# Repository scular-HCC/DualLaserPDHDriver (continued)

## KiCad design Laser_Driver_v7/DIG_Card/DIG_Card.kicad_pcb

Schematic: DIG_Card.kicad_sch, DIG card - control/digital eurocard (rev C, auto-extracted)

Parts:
A1: TEENSY_4.1; TEENSY_LONG_EXT
C80, C82, C84, C85: 100n; C_0805_2012Metric_Pad1.18x1.45mm_HandSolder
C81, C86: 100nF; C_0805_2012Metric_Pad1.18x1.45mm_HandSolder
C83, C87: 10n; C_0805_2012Metric_Pad1.18x1.45mm_HandSolder
C88, C92: 0.1uF; C_0805_2012Metric_Pad1.18x1.45mm_HandSolder
C89, C90, C91: 10nF; C_0805_2012Metric_Pad1.18x1.45mm_HandSolder
C301: 100nF U301 +15V; C_0805_2012Metric
C302: 100nF U301 -15V; C_0805_2012Metric
C303: 1n ERR1 ADC filter; C_0805_2012Metric
C304: 1n ERR2 ADC filter; C_0805_2012Metric
C305: 100nF U302 +15V; C_0805_2012Metric
C306: 100nF U302 -15V; C_0805_2012Metric
C307: 100nF U303 3V3; C_0805_2012Metric
C310: DNP MOD1 LPF; C_0805_2012Metric
C311: DNP MOD2 LPF; C_0805_2012Metric
C312: 100nF Y1 3V3_OSC; C_0805_2012Metric; MPN CL21B104KBCNNNC
C313: 1uF Y1 3V3_OSC; C_0805_2012Metric; MPN CC0805KKX7R8BB105
C314: 100nF U40 3V3; C_0805_2012Metric; MPN CL21B104KBCNNNC
C315: 100nF U41 3V3; C_0805_2012Metric; MPN CL21B104KBCNNNC
C316: 100nF U42 1V8; C_0805_2012Metric; MPN CL21B104KBCNNNC
C317: 100nF U42 3V3; C_0805_2012Metric; MPN CL21B104KBCNNNC
C318: 10uF U42 3V3; C_0805_2012Metric; MPN CC0805KKX5R7BB106
C319: 1uF U42 1V8_CLK; C_0805_2012Metric; MPN CC0805KKX7R8BB105
C320: 10nF U34 COMP; C_0805_2012Metric
C321: 10nF U39 COMP; C_0805_2012Metric
C322: 10uF +5V bulk; C_0805_2012Metric
C323: 10uF 3V3 bulk; C_0805_2012Metric
C324: 100nF 1V8 entry; C_0805_2012Metric
C325: 10uF 1V8 entry; C_0805_2012Metric
D24: BAV99; SOT-23
D301: BAT54S ERR1 ADC clamp; SOT-23
D302: BAT54S ERR2 ADC clamp; SOT-23
D303, D304, D305, D306, D307, D308, D309, D310, D311: BAT54WS VM fault OR; D_SOD-323
FB301: 600R@100MHz FB Y1; L_0805_2012Metric; MPN MPZ2012S601AT000
FB302: 600R@100MHz FB U42core; L_0805_2012Metric; MPN MPZ2012S601AT000
H1, H2: MountingHole; MountingHole_2.7mm
J2: 10MHz Ref SMA; SMA_BAT_Wireless_BWSMA-KWE-Z001
J301: DIN41612_03x32_C_Split; DIN41612_C_3x32_Male_Horizontal_THT
J302: LO1 out SMA; SMA_BAT_Wireless_BWSMA-KWE-Z001
J302B1: LO2 out SMA; SMA_BAT_Wireless_BWSMA-KWE-Z001
R104: 49R9 10MHz ref term; R_0805_2012Metric_Pad1.20x1.40mm_HandSolder
R105: 1M; R_0805_2012Metric_Pad1.20x1.40mm_HandSolder
R106: 27k; R_0805_2012Metric_Pad1.20x1.40mm_HandSolder
R107, R108, R111: 1k; R_0805_2012Metric_Pad1.20x1.40mm_HandSolder
R109: 100k; R_0805_2012Metric_Pad1.20x1.40mm_HandSolder
R110: 10M; R_0805_2012Metric_Pad1.20x1.40mm_HandSolder
R112, R113: 2.2k; R_0805_2012Metric_Pad1.20x1.40mm_HandSolder
R114: 100; R_0805_2012Metric_Pad1.20x1.40mm_HandSolder
R301, R302: 100R I2C series; R_0805_2012Metric
R303: 3k3 ERR1 ADC series; R_0805_2012Metric
R304: 3k3 ERR2 ADC series; R_0805_2012Metric
R305: 10k FAULT_n pullup; R_0805_2012Metric
R306: 47R MOD1 bus series; R_0805_2012Metric
R307: 47R MOD2 bus series; R_0805_2012Metric
R311: 33R CLK10M series; R_0805_2012Metric
R312: 49R9 LO1 series; R_0805_2012Metric
R313: 49R9 LO2 series; R_0805_2012Metric
R314: 0R MOD1 LPF (provision); R_0805_2012Metric
R315: 0R MOD2 LPF (provision); R_0805_2012Metric
R316: 33R MCLK2 series; R_0805_2012Metric
R317: 33R MCLK3 series; R_0805_2012Metric
R318: 33R MCLK1 series; R_0805_2012Metric
TP301: N_U41_B1; TestPoint_Pad_D1.0mm
TP302: N_U41_A; TestPoint_Pad_D1.0mm
TP303: CLK10M_BUF; TestPoint_Pad_D1.0mm
TP304: MCLK1; TestPoint_Pad_D1.0mm
TP305: MCLK2; TestPoint_Pad_D1.0mm
TP306: 3V3_OSC; TestPoint_Pad_D1.0mm
TP307: 1V8_CLK; TestPoint_Pad_D1.0mm
TP308: 3V3; TestPoint_Pad_D1.0mm
TP309: +5V; TestPoint_Pad_D1.0mm
TP310: 1V8; TestPoint_Pad_D1.0mm
TP311: 5Vref; TestPoint_Pad_D1.0mm
TP312: VREF_MID; TestPoint_Pad_D1.0mm
TP313: VHI; TestPoint_Pad_D1.0mm
TP314: VLO; TestPoint_Pad_D1.0mm
TP315, TP316, TP317, TP318, TP319, TP320: GND; TestPoint_THTPad_D1.5mm_Drill0.7mm
U34, U39: AD9833xRM; MSOP-10_3x3mm_P0.5mm
U35, U38: AD9833xRM (ref); MSOP-10_3x3mm_P0.5mm
U40: LMV7219M5; SOT-23-5
U41: SN74LVC1G3157DBVR; SOT-23-6_Handsoldering
U42: CDCE913PWG4; SOP65P640X120-14N
U44: CR2013-MI2120
U301: OPA192IDBVR MOD1 buffer; SOT-23-5
U302: OPA192IDBVR MOD2 buffer; SOT-23-5
U303: 74LVC1G125 CLK10M bus buffer; SOT-23-5
VM_C75, VM_C76, VM_C77, VM_C78, VM_C79, VM_C80, VM_C90: 100nF; C_0805_2012Metric_Pad1.18x1.45mm_HandSolder
VM_C81, VM_C82, VM_C83, VM_C84, VM_C85, VM_C86, VM_C87, VM_C88, VM_C89: 10nF; C_0805_2012Metric_Pad1.18x1.45mm_HandSolder
VM_D16: +15V_OK; LED_0805_2012Metric_Pad1.15x1.40mm_HandSolder
VM_D17: -15V_OK; LED_0805_2012Metric_Pad1.15x1.40mm_HandSolder
VM_D18: +5V_OK; LED_0805_2012Metric_Pad1.15x1.40mm_HandSolder
VM_D19: -5V_OK; LED_0805_2012Metric_Pad1.15x1.40mm_HandSolder
VM_D20: +6V_OK; LED_0805_2012Metric_Pad1.15x1.40mm_HandSolder
VM_D21: -6V_OK; LED_0805_2012Metric_Pad1.15x1.40mm_HandSolder
VM_D22: +5VLaser_OK; LED_0805_2012Metric_Pad1.15x1.40mm_HandSolder
VM_D23: 3V3_OK; LED_0805_2012Metric_Pad1.15x1.40mm_HandSolder
VM_D24: 1V8_OK; LED_0805_2012Metric_Pad1.15x1.40mm_HandSolder
VM_Q11, VM_Q12, VM_Q13, VM_Q14, VM_Q15, VM_Q16, VM_Q17, VM_Q18, VM_Q19: MMBT3904; SOT-23
VM_R50: 29.4k; R_0805_2012Metric_Pad1.20x1.40mm_HandSolder
VM_R51: 1k; R_0805_2012Metric_Pad1.20x1.40mm_HandSolder
VM_R52: 9.53k; R_0805_2012Metric_Pad1.20x1.40mm_HandSolder
VM_R53: 110k; R_0805_2012Metric_Pad1.20x1.40mm_HandSolder
VM_R54, VM_R55, VM_R58, VM_R60, VM_R62, VM_R63, VM_R67, VM_R69, VM_R70, VM_R73, VM_R75, VM_R76, VM_R79, VM_R80, VM_R81, VM_R82, VM_R84, VM_R85, VM_R86, VM_R87: 10k; R_0805_2012Metric_Pad1.20x1.40mm_HandSolder
VM_R56, VM_R66, VM_R72: 100; R_0805_2012Metric_Pad1.20x1.40mm_HandSolder
VM_R59: 120k; R_0805_2012Metric_Pad1.20x1.40mm_HandSolder
VM_R61: 40.2k; R_0805_2012Metric_Pad1.20x1.40mm_HandSolder
VM_R64: 47.5k; R_0805_2012Metric_Pad1.20x1.40mm_HandSolder
VM_R65, VM_R77: 30.1k; R_0805_2012Metric_Pad1.20x1.40mm_HandSolder
VM_R71: 38.3k; R_0805_2012Metric_Pad1.20x1.40mm_HandSolder
VM_R78: 16.5k; R_0805_2012Metric_Pad1.20x1.40mm_HandSolder
VM_R83: 4.42k; R_0805_2012Metric_Pad1.20x1.40mm_HandSolder
VM_R88, VM_R89, VM_R90, VM_R91, VM_R92, VM_R93, VM_R94, VM_R95, VM_R96: 1.3k; R_0805_2012Metric_Pad1.20x1.40mm_HandSolder
VM_R97, VM_R98, VM_R99, VM_R100, VM_R101, VM_R102, VM_R103, VM_R104, VM_R105: 4.7k; R_0805_2012Metric_Pad1.20x1.40mm_HandSolder
VM_U22: MCP6002-xSN; SOIC-8_3.9x4.9mm_P1.27mm
VM_U23, VM_U25, VM_U26, VM_U27, VM_U28: LM339B; SOIC-14_3.9x8.7mm_P1.27mm
VM_U24: MCP6004; SOIC-14_3.9x8.7mm_P1.27mm
Y1: ASE-10.000MHZ-LC-T; XTAL_ASE-10.000MHZ-LC-T

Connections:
1V8: C324.1, C325.1, FB302.2, J301.a17, J301.b17, J301.c17, R111.1, TP310.1 (1_1), VM_C81.2, VM_R83.1, VM_U28.9 (+), VM_U28.11 (+)
1V8_CLK: C316.1, C319.1, FB302.1, TP307.1 (1_1), U42.3 (VDD)
3.3V: A1.3V3 (3.3V), A1.3V3@2 (3.3V), A1.3V3@3 (3.3V)
3V3: C80.2, C84.2, C88.2, C92.2, C307.1, C314.1, C315.1, C317.1, C318.1, C323.1, D301.2 (K), D302.2 (K), FB301.1, J301.a16, J301.b16, J301.c16, R105.1, R112.2, R113.2, R114.2, R305.1, TP308.1 (1_1), U34.2 (VDD), U35.2 (VDD), U38.2 (VDD), U39.2 (VDD), U40.5 (V+), U41.5 (VCC), U42.6 (VDDOUT), U42.7 (VDDOUT), U44.1 (VCC), U303.5 (VCC), VM_R78.1
3V3_OSC: C312.1, C313.1, FB301.2, TP306.1 (1_1), Y1.1 (TRI-STATE(STBY)), Y1.4 (VDD)
5Vref: J301.a20, TP311.1 (1_1), VM_R50.1
+5V: A1.VIN, C322.1, J301.a13, J301.b13, J301.c13, TP309.1 (1_1), VM_C75.1, VM_C76.1, VM_C77.1, VM_C78.1, VM_C79.1, VM_C80.1, VM_C90.1, VM_R65.1, VM_R84.1, VM_R88.1, VM_R89.1, VM_R90.1, VM_R91.1, VM_R92.1, VM_R93.1, VM_R94.1, VM_R95.1, VM_R96.1, VM_R97.2, VM_R98.2, VM_R99.2, VM_R100.2, VM_R101.2, VM_R102.2, VM_R103.2, VM_R104.2, VM_R105.2, VM_U22.8 (V+), VM_U23.3 (V+), VM_U24.4 (V+), VM_U25.3 (V+), VM_U26.3 (V+), VM_U27.3 (V+), VM_U28.3 (V+)
+5V_LASER: J301.a15, J301.b15, J301.c15, VM_R77.1
+6V_TEC: J301.a1, J301.a2, J301.b1, J301.b2, J301.c1, J301.c2, VM_R71.1
+15V: C301.1, C305.1, J301.a11, J301.b11, J301.c11, U301.5 (V+), U302.5 (V+), VM_R53.1
+18V: J301.a7, J301.b7, J301.c7
-5V: J301.a14, J301.b14, J301.c14, VM_R61.1
-6V_TEC: J301.a5, J301.a6, J301.b5, J301.b6, J301.c5, J301.c6, VM_R64.1
-15V: C302.1, C306.1, J301.a12, J301.b12, J301.c12, U301.2 (V-), U302.2 (V-), VM_R59.1
-18V: J301.a9, J301.b9, J301.c9
/CLK10M_BUF: R311.1, TP303.1 (1_1), U303.4 (Y)
/DDS1_FSYNC: A1.D2, U34.8 (~FSYNC)
/DDS2_FSYNC: A1.D3, U39.8 (~FSYNC)
/DDS3_FSYNC: A1.D6, U35.8 (~FSYNC)
/DDS4_FSYNC: A1.D8, U38.8 (~FSYNC)
/ERR1_ADC: A1.D24 (A10), C303.1, D301.3 (COM), R303.2
/ERR2_ADC: A1.D25 (A11), C304.1, D302.3 (COM), R304.2
/LO1_OUT: J302.1 (In), R312.2
/LO2_OUT: J302B1.1 (In), R313.2
/MCLK1: R318.2, TP304.1 (1_1), U34.5 (MCLK), U35.5 (MCLK)
/MCLK1_S: R318.1, U42.11 (Y1)
/MCLK2: R316.2, TP305.1 (1_1), U38.5 (MCLK), U39.5 (MCLK)
/MCLK2_S: R316.1, U42.9 (Y2)
/MCLK3: A1.D9, R317.2
/MCLK3_S: R317.1, U42.8 (Y3)
/MOD1_BUF: R306.1, U301.1 (OUT), U301.4 (IN-)
/MOD1_IN: C310.1, R314.2, U301.3 (IN+)
/MOD2_BUF: R307.1, U302.1 (OUT), U302.4 (IN-)
/MOD2_IN: C311.1, R315.2, U302.3 (IN+)
/MOSI_3V3: A1.D11 ((SDO)D11), U34.6 (SDATA), U35.6 (SDATA), U38.6 (SDATA), U39.6 (SDATA)
/N_C89_Pad2: C89.2, R107.1
/N_C90_Pad2: C90.2, R108.1
/N_D24_A: C91.2, D24.3 (K), R109.1, R110.1, U40.3 (+)
/N_D24_K_Pad1: D24.1 (K), R108.2
/N_J2A_In1: C89.1, C90.1, J2.1 (In), R104.2
/N_U34_CAP/2_5V: C81.2, U34.3 (CAP/2.5V)
/N_U34_COMP: C320.1, U34.1 (COMP)
/N_U35_CAP/2_5V: C82.2, U35.3 (CAP/2.5V)
/N_U35_COMP: C83.1, U35.1 (COMP)
/N_U38_CAP/2_5V: C85.2, U38.3 (CAP/2.5V)
/N_U38_COMP: C87.1, U38.1 (COMP)
/N_U39_CAP/2_5V: C86.2, U39.3 (CAP/2.5V)
/N_U39_COMP: C321.1, U39.1 (COMP)
/N_U40__: R105.2, R106.1, U40.4 (-)
/N_U41_A: TP302.1 (1_1), U41.4 (A), U42.1 (XIN/CLK), U303.2 (A)
/N_U41_B1: TP301.1 (1_1), U41.3 (B1), Y1.3 (OUTPUT)
/N_U41_B2: R107.2, U41.1 (B2)
/N_U41_S: R110.2, U40.1, U41.6 (S)
/N_U42_S0: R111.2, U42.2 (S0)
/N_U44_D/~C: A1.D29, U44.5 (D/~C)
/N_U44_RESET: A1.D30, U44.4 (RESET)
/N_U44_~CS: A1.D28, U44.3 (~CS)
/OLD_AD5064_CLR: A1.D7
/OLD_CS_3V3: A1.D10 ((CS)D10)
/OLD_HBridgeFault2: A1.D32
/OLD_LAS2_IMON: A1.D22 (A8)
/OLD_LOCK1_EN: A1.D33
/OLD_LOCK2_EN: A1.D34
/OLD_MPD1_MON: A1.D17 (A3)
/OLD_MPD2_MON: A1.D23 (A9)
/OLD_NTC2_A: A1.D20 (A6)
/OLD_NTC_A14: A1.D38 (A14)
/OLD_TEC2_IMON: A1.D21 (A7)
/SCK_3V3: A1.D13 ((CLK)D13), U34.7 (SCLK), U35.7 (SCLK), U38.7 (SCLK), U39.7 (SCLK)
/TFT_MOSI: A1.D26 (A12), U44.6 (MOSI)
/TFT_SCK: A1.D27 (A13), U44.7 (SCK)
/VHI_Buf: TP313.1 (1_1), VM_U22.1, VM_U22.2 (-), VM_U23.5 (+), VM_U23.11 (+), VM_U25.5 (+), VM_U25.11 (+), VM_U26.5 (+), VM_U26.11 (+), VM_U27.5 (+), VM_U27.11 (+), VM_U28.5 (+)
/VLO_Buf: TP314.1 (1_1), VM_U22.6 (-), VM_U22.7, VM_U23.6 (-), VM_U23.8 (-), VM_U25.6 (-), VM_U25.8 (-), VM_U26.6 (-), VM_U26.8 (-), VM_U27.6 (-), VM_U27.8 (-), VM_U28.6 (-)
/VM_N_D16_A: VM_D16.2 (A), VM_R96.2
/VM_N_D16_K: VM_D16.1 (K), VM_Q11.3 (C)
/VM_N_D17_A: VM_D17.2 (A), VM_R95.2
/VM_N_D17_K: VM_D17.1 (K), VM_Q12.3 (C)
/VM_N_D18_A: VM_D18.2 (A), VM_R94.2
/VM_N_D18_K: VM_D18.1 (K), VM_Q13.3 (C)
/VM_N_D19_A: VM_D19.2 (A), VM_R93.2
/VM_N_D19_K: VM_D19.1 (K), VM_Q14.3 (C)
/VM_N_D20_A: VM_D20.2 (A), VM_R92.2
/VM_N_D20_K: VM_D20.1 (K), VM_Q15.3 (C)
/VM_N_D21_A: VM_D21.2 (A), VM_R91.2
/VM_N_D22_A: VM_D22.2 (A), VM_R88.2
/VM_N_D22_K: VM_D22.1 (K), VM_Q17.3 (C)
/VM_N_D23_K: VM_D23.1 (K), VM_Q18.3 (C)
/VM_N_D24_A: VM_D24.2 (A), VM_R90.2
/VM_N_D24_K: VM_D24.1 (K), VM_Q19.3 (C)
/VM_N_Q11_B: VM_Q11.1 (B), VM_R55.2
/VM_N_Q12_B: VM_Q12.1 (B), VM_R58.2
/VM_N_Q13_B: VM_Q13.1 (B), VM_R69.2
/VM_N_Q14_B: VM_Q14.1 (B), VM_R70.2
/VM_N_Q15_B: VM_Q15.1 (B), VM_R75.2
/VM_N_Q16_B: VM_Q16.1 (B), VM_R76.2
/VM_N_Q17_B: VM_Q17.1 (B), VM_R81.2
/VM_N_Q18_B: VM_Q18.1 (B), VM_R82.2
/VM_N_Q19_B: VM_Q19.1 (B), VM_R87.2
/VM_N_R55_Pad1: D303.1 (K), VM_R55.1, VM_R97.1, VM_U23.1, VM_U23.2
/VM_N_R56_Pad1: VM_R56.1, VM_R60.2, VM_U24.1
/VM_N_R58_Pad1: D304.1 (K), VM_R58.1, VM_R98.1, VM_U23.13, VM_U23.14
/VM_N_R62_Pad2: VM_R62.2, VM_R66.1, VM_U24.7
/VM_N_R63_Pad2: VM_R63.1, VM_R72.1, VM_U24.8
/VM_N_R69_Pad1: D305.1 (K), VM_R69.1, VM_R99.1, VM_U25.1, VM_U25.2
/VM_N_R100_Pad1: D306.1 (K), VM_R70.1, VM_R100.1, VM_U25.13, VM_U25.14
/VM_N_R101_Pad1: D307.1 (K), VM_R75.1, VM_R101.1, VM_U26.1, VM_U26.2
/VM_N_R102_Pad1: D308.1 (K), VM_R76.1, VM_R102.1, VM_U26.13, VM_U26.14
/VM_N_R103_Pad1: D309.1 (K), VM_R87.1, VM_R103.1, VM_U28.1, VM_U28.2
/VM_N_R104_Pad1: D310.1 (K), VM_R82.1, VM_R104.1, VM_U27.13, VM_U27.14
/VM_N_R105_Pad1: D311.1 (K), VM_R81.1, VM_R105.1, VM_U27.1, VM_U27.2
/VM_N_U23A__: VM_C84.1, VM_R53.2, VM_R54.1, VM_U23.4 (-), VM_U23.7 (+)
/VM_N_U23C__: VM_C85.1, VM_R56.2, VM_U23.9 (+), VM_U23.10 (-)
/VM_N_U24A__: VM_R59.2, VM_R60.1, VM_U24.2 (-)
/VM_N_U24B__: VM_R61.2, VM_R62.1, VM_U24.6 (-)
/VM_N_U24C__: VM_R63.2, VM_R64.2, VM_U24.9 (-)
/VM_N_U24D_P: VM_R84.2, VM_R86.1, VM_U24.12 (+)
/VM_N_U24D__: VM_U24.13 (-), VM_U24.14
/VM_N_U25A__: VM_C86.1, VM_R65.2, VM_R67.1, VM_U25.4 (-), VM_U25.7 (+)
/VM_N_U25C__: VM_C87.1, VM_R66.2, VM_U25.9 (+), VM_U25.10 (-)
/VM_N_U26A__: VM_C88.1, VM_R71.2, VM_R73.1, VM_U26.4 (-), VM_U26.7 (+)
/VM_N_U26C__: VM_C89.1, VM_R72.2, VM_U26.9 (+), VM_U26.10 (-)
/VM_N_U27A__: VM_C83.1, VM_R77.2, VM_R79.1, VM_U27.4 (-), VM_U27.7 (+)
/VM_N_U27C__: VM_C82.1, VM_R78.2, VM_R80.1, VM_U27.9 (+), VM_U27.10 (-)
/VM_N_U28A__: VM_C81.1, VM_R83.2, VM_R85.1, VM_U28.4 (-), VM_U28.7 (+)
/_VoltageMonitor_VHI: VM_R50.2, VM_R51.1, VM_U22.3 (+)
/_VoltageMonitor_VLO: VM_R51.2, VM_R52.1, VM_U22.5 (+)
CLK10M_BUS: J301.c28, R311.2
ERR1_BUS: J301.c20, R303.1
ERR2_BUS: J301.c22, R304.1
FAULT_n: A1.D31, D303.2 (A), D304.2 (A), D305.2 (A), D306.2 (A), D307.2 (A), D308.2 (A), D309.2 (A), D310.2 (A), D311.2 (A), J301.a24, R305.2
GND: A1.AGND/GND (GND), A1.GND, A1.GND@2 (GND), C80.1, C81.1, C82.1, C83.2, C84.1, C85.1, C86.1, C87.2, C88.1, C91.1, C92.1, C301.2, C302.2, C303.2, C304.2, C305.2, C306.2, C307.2, C310.2, C311.2, C312.2, C313.2, C314.2, C315.2, C316.2, C317.2, C318.2, C319.2, C320.2, C321.2, C322.2, C323.2, C324.2, C325.2, D301.1 (A), D302.1 (A), J2.2 (Ext), J301.a8, J301.a10, J301.a18, J301.a19, J301.a21, J301.a23, J301.a25, J301.a27, J301.a29, J301.b8, J301.b10, J301.b18, J301.b19, J301.b20, J301.b21, J301.b22, J301.b23, J301.b24, J301.b25, J301.b26, J301.b27, J301.b28, J301.b29, J301.b30, J301.b31, J301.b32, J301.c8, J301.c10, J301.c18, J301.c19, J301.c21, J301.c23, J301.c25, J301.c27, J301.c29, J302.2 (Ext), J302B1.2 (Ext), R104.1, R106.2, R109.2, TP315.1 (1_1), TP316.1 (1_1), TP317.1 (1_1), TP318.1 (1_1), TP319.1 (1_1), TP320.1 (1_1), U34.4 (DGND), U34.9 (AGND), U35.4 (DGND), U35.9 (AGND), U38.4 (DGND), U38.9 (AGND), U39.4 (DGND), U39.9 (AGND), U40.2 (V-), U41.2 (GND), U42.5 (GND), U42.10 (GND), U44.2 (GND), U303.1 (~OE), U303.3 (GND), VM_C75.2, VM_C76.2, VM_C77.2, VM_C78.2, VM_C79.2, VM_C80.2, VM_C82.2, VM_C83.2, VM_C84.2, VM_C85.2, VM_C86.2, VM_C87.2, VM_C88.2, VM_C89.2, VM_C90.2, VM_Q11.2 (E), VM_Q12.2 (E), VM_Q13.2 (E), VM_Q14.2 (E), VM_Q15.2 (E), VM_Q16.2 (E), VM_Q17.2 (E), VM_Q18.2 (E), VM_Q19.2 (E), VM_R52.2, VM_R54.2, VM_R67.2, VM_R73.2, VM_R79.2, VM_R80.2, VM_R85.2, VM_R86.2, VM_U22.4 (V-), VM_U23.12 (V-), VM_U24.3 (+), VM_U24.5 (+), VM_U24.10 (+), VM_U24.11 (V-), VM_U25.12 (V-), VM_U26.12 (V-), VM_U27.12 (V-), VM_U28.8 (-), VM_U28.10 (-), VM_U28.12 (V-), Y1.2 (GND/CASE)
LO1_REF: R312.1, U35.10 (VOUT)
LO2_REF: R313.1, U38.10 (VOUT)
MOD1_BUS: J301.c24, R306.2
MOD1_FILT: R314.1, U34.10 (VOUT)
MOD2_BUS: J301.c26, R307.2
MOD2_FILT: R315.1, U39.10 (VOUT)
unnamed: R114.1, U44.8 (LED)
unnamed: VM_D21.1 (K), VM_Q16.3 (C)
unnamed: VM_D23.2 (A), VM_R89.2
PGND_TEC: J301.a3, J301.a4, J301.b3, J301.b4, J301.c3, J301.c4
SCL: A1.D19 (A5), R113.1, R302.2, U42.12 (S2/SCL)
SCL_BUS: J301.a28, R302.1
SDA: A1.D18 (A4), R112.1, R301.2, U42.13 (S1/SDA)
SDA_BUS: J301.a26, R301.1
SPARE_A30: J301.a30
SPARE_A31: J301.a31
SPARE_A32: J301.a32
SPARE_C30: J301.c30
SPARE_C31: J301.c31
SPARE_C32: J301.c32
VREF_MID: J301.a22, TP312.1 (1_1)

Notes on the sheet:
I2C: Teensy = master; MCU_SDA/SCL merged onto card net SDA/SCL (also serves CDCE913); bus pullups = existing R112/R113 4.7k (Clock sheet) - the ONLY pullups on the whole backplane bus.
VoltageMonitor windows +/-15V, +/-5V, +/-6V_TEC, +5V_LASER, 3V3, 1V8. +/-18V blades (P5-P8) pass through UNMONITORED.
OLD_* nets = Teensy pins freed by the I2C migration (monitors, LOCK_EN, faults, CS/CLR, PowerNTC) - reassign in firmware pass.
I2C pullups R112/R113 4.7k -> 2.2k (sole pullups for 8-slot bus); VM fault nodes diode-ORed onto FAULT_n (D303-D311,
Wiring by net label at every pin (no graphic wires). AD5064 U37 REMOVED - setpoints now on-card I2C DACs (CH cards).
R110 = ext-ref auto-select hysteresis (hold = 3V3*R109 / (R110+R109), R109=100k; U40 trip = +86.8mV): 10M (fitted): hold ~33mV < trip -> releases when ext ref unplugged 1M: hold ~300mV > trip -> latches to ext until power-cycle 0R: node tied to U40 OUT -> hard latch, defeats auto-detect
DDS MOD-LO GEN (v3, no AD5064)
is this clock buffer needed?
LO SMAs get 49R9 back-termination (R312/R313); MOD LPF provision R314/R315 0R + C310/C311 DNP ahead of buffers.
LO1/LO2 out via J302 front SMAs (coax to AFE card). 10MHz ref on Clock J2 as in v3.
BAT54WS, node LOW = rail fault pulls bus); 10MHz mux output buffered to bus c20 (U303 74LVC1G125 + R311 33R);
ASSEMBLY: CUT the VUSB-VIN pad on the Teensy 4.1 - otherwise plugging USB drives 5V onto the crate +5V rail.
CARD ADDRESS via on-card jumpers JP301-JP303 (10k pullups R308-R310 to 3V3): fit jumper = 0, open = 1.
Backplane GA pins a20/c18/c19 (GA*_BP) intentionally unused - address lives on the card (scheme change 2026-07-16).
GA0/GA1/GA2 = Teensy pins 14/15/16 (freed A0/A1/A2); FAULT_n = Teensy pin 31 (was HBridgeFault1) - matches firmware config.h.
TEENSY + TFT (v3)
ERR1/ERR2_BUS -> 3k3/1n RC + BAT54S clamp -> Teensy ADC (ERRn_ADC). Restores v3 R118/C98 dropped in the port.
REV C cleanups: U36 74AHCT125 deleted (fed removed AD5064); R3/R4/C3 PowerNTC divider deleted (A1.D38 -> OLD_NTC_A14);
REV C (2026-07-19): U301/U302 now real SOT-23-5 OPA192 symbol (v3 LT1028_2 numbering matched no package);
Teensy VIN moved 3V3 -> +5V (a16); ERR bus conditioned: 3k3 (R303/R304) + 1n (C303/C304) + BAT54S clamps (D301/D302).
DIG CARD rev C - v3 Teensy/laser_control/Clock + VoltageMonitor (power board, refs VM_*) + universal bus IF.
MOD buses buffered: DDS out (MODn_FILT) -> U301/U302 OPA192 follower -> 47R -> MODn_BUS.
BUS INTERFACE (new)

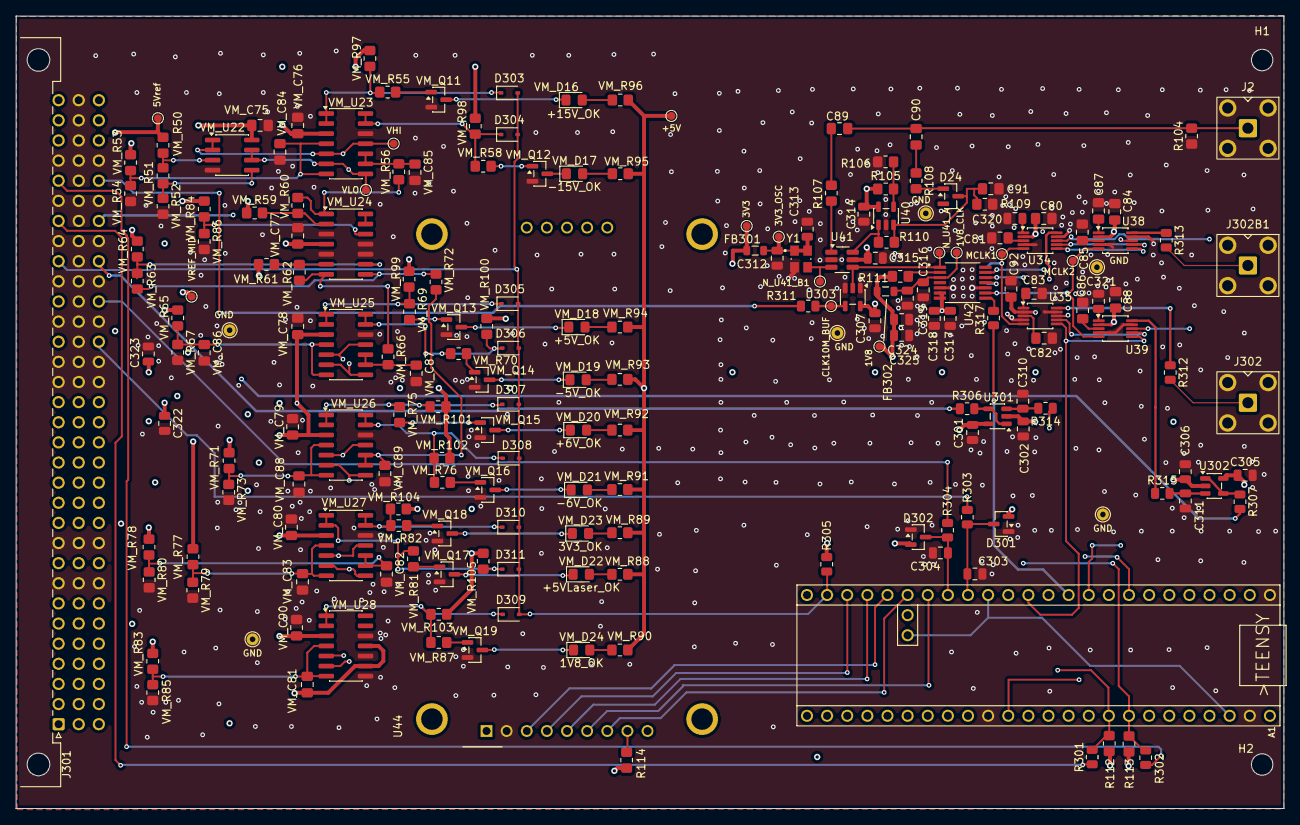
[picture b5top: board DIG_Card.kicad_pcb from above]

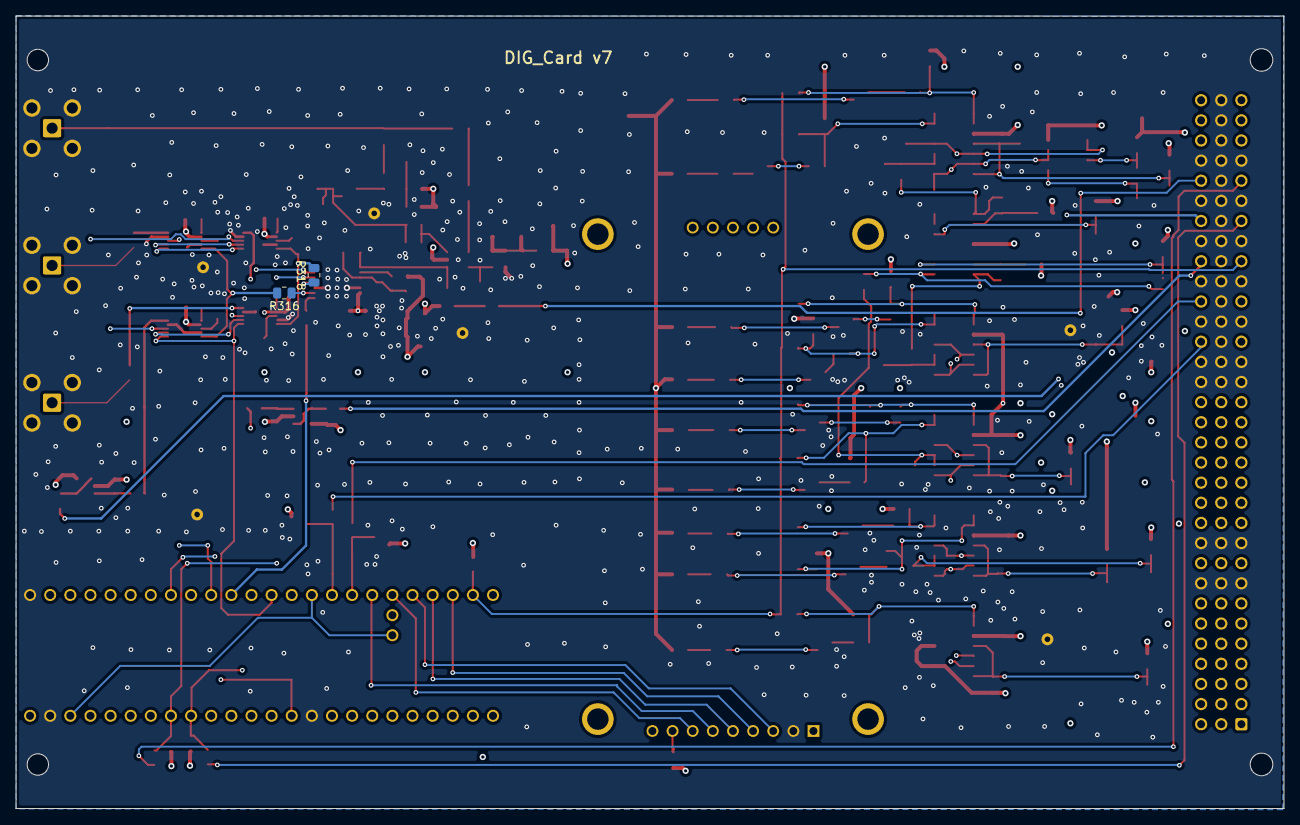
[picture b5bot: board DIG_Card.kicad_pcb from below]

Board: 6 copper layers, 160.0 x 100.0 mm, 209 parts (2 on the bottom side), 135 nets.
